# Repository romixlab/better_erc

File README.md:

# better_erc

Electrical rule checks for schematics that go further than the ERC built into an EDA tool: checks that know
what an I2C bus, a pull-up, a MOSFET or a power rail is, read from the netlist your EDA tool exports. Plus
`berc textconv`, which makes `git diff` of KiCad files readable.

For hardware engineers who review schematics (their own or someone else's) and want the repetitive part of a
review done by a tool, and for teams that keep KiCad projects in git.

The project is early. The KiCad diff tool is ready for daily use; the checks run from the shell and in CI with
`berc check` and as a Rust library; the desktop app is a first prototype.

## What works today

- **`berc textconv`**: `.kicad_sch`, `.kicad_pcb` and `.kicad_pro` files as sorted, line-oriented text for
  `git diff`, `git log -p` and anything else that uses git's textconv. See
  [Readable git diffs](#readable-git-diffs).
- **Import** into one board model ([docs/model.md](docs/model.md)): KiCad 8, 9 and 10 projects, schematics, boards
  and netlists read by better_erc itself (`erc_kicad`), OrCAD Capture netlists (pstxnet, pstxprt, pstchip), Altium
  EDIF plus WireList, Altium Smart PDFs (the netlist in their bookmarks: vendor boards that come as nothing but a
  PDF), and pick-and-place CSV files from KiCad, Altium and Allegro (`erc_import`), all picked by one importer
  registry.
- **Checks** (`erc_checks`), run on a KiCad project read by better_erc itself (`erc_kicad`), with one finding
  type, a report of which checks ran and which could not run for lack of data, and the report as JSON or text
  ([docs/engine.md](docs/engine.md)):
  - I2C buses found from net names, including segments behind ties and voltage translators; missing, redundant,
    unequal or out-of-range pull-ups, pull-ups through series resistors to nowhere, series resistors that are
    too large (`I2C-1`, `I2C-2`, `I2C-3`, `I2C-7`, `I2C-9`, `I2C-10`)
  - parts without a value, placeholder values like `?` or `TBD` (fitted or not), resistor values that don't read
    or are written in a non-standard way (`BOM-5`, `BOM-6`, `BOM-9`, `BOM-10`)
  - MOSFET symbols whose pins aren't named G, S and D (`LIB-3`)
- **`berc check`**: the checks on a KiCad project (or a KiCad netlist, Altium, OrCAD, Smart PDF or PnP file) from the shell
  or a CI job, as text, JSON, SARIF (GitHub code scanning) or Markdown (a PR comment), with an exit code by
  severity and a baseline so only new findings fail. `berc explain ID` and `berc checks list` show the catalogue.
  See [Checks in CI](#checks-in-ci).
- **`berc diff --pnp A B`**: two pick-and-place files, two boards, or a board and the PnP file exported from it
  compared footprint by footprint (position, rotation, side, value, package), with tolerances.
- **`berc diff --nets A B`**: the nets of any two designs (a schematic, a netlist, an Altium export, a Smart PDF)
  compared as the pins each net connects, whatever their names: renamed, removed and added nets.
- **`berc fp`**: footprint review. `berc fp hash` prints a footprint's review hash, the same for a library file and
  every board copy of it; `berc fp check` checks every board footprint against the hash on its library symbol (and
  against its library footprint), `berc fp check --lib` every symbol of a symbol library against its library
  footprint, and `berc fp todo` lists the library symbols a board uses that need a review; `berc fp model` reads
  each footprint's 3D models and measures them against it. See [Footprint review](#footprint-review).
- **The app** (`better_erc`, egui, crate `better_erc_app`): an import tab that opens any design the registry reads
  (and Altium or OrCAD files picked one by one) and shows its findings with their explanations and the checks that
  did not run, and tabs for nets (power rails, grounds and switching nodes from names and pin types), I2C buses,
  style findings and inputs; a footprint review tab that draws a library symbol's footprint over its datasheet
  drawing and writes the review hash into the symbol (see [Reviewing in the app](#reviewing-in-the-app)).
- **Signal levels** (crate `erc_levels`): a database of the levels logic families, buses and differential
  standards define (74xx and CD4000, JEDEC LVCMOS/SSTL/HSTL, I2C, RS-485, CAN, LVDS, ECL, USB, Ethernet and more),
  every number with the document, table and page it was read from. See [docs/signal-levels.md](docs/signal-levels.md).
- **The library** (crate `better_erc`): all of the above for Rust code in one dependency.

## Documentation

- [docs/checks.md](docs/checks.md): the check catalogue, everything better_erc should catch on a schematic or
  netlist, by ID (`PIN-1`, `I2C-3`) and severity.
- [docs/engine.md](docs/engine.md): the check engine: checks and their data needs, findings, the report, the test
  schematics with their expectations, how to add a check.
- [docs/model.md](docs/model.md): the board model, the importers and the crates.
- [docs/drawing-guide.md](docs/drawing-guide.md): how to draw a sheet that reads at a glance (signal flow, power and
  ground, grid, labels, text, title block, KiCad shortcuts), each rule with its reason and source, and our own sheets
  measured against it; the `DRAW` checks automate part of it.
- [docs/signal-levels.md](docs/signal-levels.md): the signal-level database: its format, where each number comes
  from, what `verified` means, and how to add a family.
- [docs/review-checklist.md](docs/review-checklist.md): a condensed schematic review checklist that groups those
  IDs for a review pass.
- [FEATURES.md](FEATURES.md): what the code does today and what is planned, item by item.
- [CHANGELOG.md](CHANGELOG.md): what changed in each version.

## Install

You need a Rust toolchain (1.86 or newer, from [rustup](https://rustup.rs)). From a clone of this repository, with
[just](https://github.com/casey/just): `just install` works anywhere and builds both binaries; with our release
tool on PATH it uses that (one copy kept on PATH), otherwise `cargo install`. Or by hand:

```sh
cargo install --locked --path berc             # the berc command line tool
cargo install --locked --path better_erc_app   # the desktop app (binary better_erc)
```

`berc --version` shows the version,
the git commit it was built from and that commit's time.

## Quick start

Readable diffs of a KiCad project in git, once per machine and once per repository:

```sh
git config --global diff.kicad.textconv "berc textconv"
printf '*.kicad_sch diff=kicad\n*.kicad_pcb diff=kicad\n*.kicad_pro diff=kicad\n' >> .gitattributes
git diff   # changed parts, values, nets and settings instead of raw s-expressions
```

Run the checks on a KiCad project (its directory, or the `.kicad_pro` / `.kicad_sch`):

```sh
berc check hw/board                  # findings worst first, the checks that could not run and why
berc explain I2C-3                   # what a check catches, why it matters, how to fix it
berc checks list --project hw/board  # every catalogue check: ran, not run (and why), planned
```

From Rust, the same run is `erc_checks::check_path` (or `erc_checks::Project::open` and `check`), see
[docs/engine.md](docs/engine.md).

Start the app with `just run` (or `better_erc` once installed).

Shell completion for `berc`: add `source <(COMPLETE=bash berc)` to `~/.bashrc`, `source <(COMPLETE=zsh berc)`
to `~/.zshrc`, or `COMPLETE=fish berc | source` to `~/.config/fish/config.fish`.

## Checks in CI

```sh
berc check PROJECT [--variant V] [--only CAT,ID] [--format text|json|sarif|md]
                   [--baseline report.json] [--fail-on error|warning|suggestion] [--require NEED]
                   [--set NAME=VALUE] [--theme THEME.json]
```

`PROJECT` is a directory with one design in it (its `.kicad_pro`) or a design file. Exit codes:

| code | meaning |
|---|---|
| 0 | no finding at or above `--fail-on` (default `error`) |
| 1 | findings at or above `--fail-on`; with `--baseline`, only findings that are not in the baseline count |
| 2 | usage or import error: no such path, several designs in the directory, an unreadable file, an unknown variant or check, a baseline of another schema |
| 3 | a `--require`d need is not available on a board (`--require layout` without a `.kicad_pcb`); wins over 1 |

`--format json` writes the report with its versioned schema; that file is also what `--baseline` takes: findings are
matched by board and fingerprint (check id and the names of the nets and parts involved), marked new or unchanged,
and the fixed ones listed. `--format sarif` writes SARIF 2.1.0: one rule per catalogue check, error → `error`,
warning → `warning`, suggestion → `note`, each finding located at the schematic file and the line of its symbol
(the file alone where no line is known). `--format md` is a summary for a pull request comment. `--state` is
reserved for power states and refused until they exist.

A GitHub Actions job that fails on errors, shows the findings in code scanning on the schematic files and puts the
Markdown summary on the run page:

```yaml
name: schematic checks
on: [push, pull_request]
jobs:
  berc:
    runs-on: ubuntu-latest
    permissions:
      contents: read
      security-events: write # upload SARIF to code scanning
    steps:
      - uses: actions/checkout@v4
      - uses: dtolnay/rust-toolchain@stable
      - run: cargo install --locked --git https://github.com/romixlab/better_erc berc
      - name: berc check
        run: berc check hw/board --format sarif > berc.sarif
      - name: Summary
        if: always()
        run: berc check hw/board --format md >> "$GITHUB_STEP_SUMMARY" || true
      - name: Upload to code scanning
        if: always()
        uses: github/codeql-action/upload-sarif@v3
        with:
          sarif_file: berc.sarif
          category: better_erc
```

Run it from the repository root with a relative project path: the SARIF file names the schematic files relative to
the current directory, which is what code scanning expects. To adopt better_erc on a board with known findings,
commit a baseline (`berc check hw/board --format json > hw/board/berc-baseline.json`) and add
`--baseline hw/board/berc-baseline.json`: from then on only new findings fail the job.

In this repository `just check` runs `berc check` on the test schematics against the committed
`test_schematics/berc-baseline.json` (they have findings on purpose), and `just check-baseline` rewrites it.

## Footprint review

A footprint checked once against its datasheet should not have to be checked again on the next board, unless it
changed. `berc fp` keeps that record as a hash on the library symbol.

`berc fp hash` prints a footprint's review hash, `fp1:` and 16 hex digits:

```sh
berc fp hash Lib.pretty/SOT-23.kicad_mod          # a library footprint
berc fp hash board.kicad_pcb U3                   # a footprint on a board, by its reference
berc fp hash board.kicad_pcb U3 --canonical       # and the text the hash is taken over
```

The hash covers what a review checks against the datasheet:

- every pad: number, type, shape, size, position, rotation, drill and its offset, layers, mask, paste, clearance and
  thermal settings, corner and chamfer ratios, custom pad shapes;
- the footprint's clearance, mask and paste settings;
- graphics on copper, mask, paste, courtyard and `Edge.Cuts` layers, zones and keepouts.

Silk, fab and user layers, texts, the 3D model and where the footprint sits on a board don't count. A board copy is
brought back to the footprint's own frame first (position, rotation and a flip to the back undone), so it has the hash
of its library file. Lengths are compared on a 100 nm grid and items in a fixed order, so a re-save in another KiCad
version or a reorder never changes the hash. The `fp1:` prefix is the version of these rules: a later change of them
gives `fp2:` hashes, and an `fp1:` hash then reads as made by another version instead of as a mismatch. The hex digits
are the first 8 bytes of the SHA-256 of the canonical text (`--canonical`, lines joined by a newline): a short
fingerprint to tell a footprint unchanged, not a signature.

Once a footprint is reviewed, `berc fp accept` puts its hash in the `Footprint_Review` field of the library symbol
that uses it (see [Accepting a review](#accepting-a-review)), or the app's Accept does. `berc fp check` then checks a
board:

```sh
berc fp check                       # the KiCad project in this directory
berc fp check hw/board --format json
```

For each footprint on the board it reads the review hash from its symbol's library symbol: in the `.kicad_sym`
found through the project's or the global `sym-lib-table`, else in the schematic's copy of the library symbol. Each
footprint is one of:

| Status | Meaning |
|---|---|
| ok | the footprint is the one reviewed |
| changed | the footprint differs from the one reviewed: review it again (with several review lines, the stale ones are named) |
| partial | every review line's hash matches, but some of the symbol's MPNs are on no line: their datasheets are not reviewed yet, named |
| unreviewed | the symbol has no review hash; the line shows the hash to put there once reviewed |
| refused | the symbol sets no footprint, so a review of the one on the board means nothing |
| no symbol | the footprint has no schematic symbol and is not marked board-only |
| board-only | no symbol, marked board-only in KiCad (logos, mounting holes): listed last under its own heading, not a failure |
| other version, malformed | the field holds a hash of another version, or no hash at all |

A schematic copy that holds a different hash than the library is reported as well: the schematic was not updated
from the library. So is a board copy that differs from its library footprint (the footprint the board names, found
through `--footprints` and the `fp-lib-table`; a board footprint without a library nickname is looked up by its
symbol's `Footprint` field): the line shows both hashes, and the board was not updated from the library.

A board footprint placed under a different `Lib:Name` than its symbol's own `Footprint` field (a library migration
half done, or a deliberate per-instance override) is reported too, naming both: a library migration that renamed or
moved a footprint library, left half done, or a board edited by hand without updating the schematic, looks exactly
like this. A footprint placed with no library nickname at all is not an override, there being nothing to compare its
name against. Footprints that could not be compared are summed up once per reason below the list. `--symbols DIR` adds symbol libraries (a
`.kicad_sym`, a `.kicad_symdir` or a folder of them, each named by its file name) searched before the
`sym-lib-table`, and `--footprints DIR` footprint libraries searched before the `fp-lib-table`, for a PC without
KiCad's global tables:

```sh
berc fp check hw/board --symbols ~/kicad-library/symbols --footprints ~/kicad-library/footprints
```

The exit code is 0 when every footprint is ok or board-only and every copy up to date, 1 otherwise, 2 when the
project can't be read.

### Review lines: where a review was made

A review is made against one datasheet, and a datasheet is one maker's: the MPNs of one maker usually share one, and
two makers never do. So a symbol holds one review line per datasheet, each in a property of its own,
`Footprint_Review`, `Footprint_Review2`, `Footprint_Review3`, ... (KiCad needs field names unique, as with `Mpn1`,
`Mpn2`). Each is one line, the review hash first and where the review was made after it:

```text
fp1:7726812df851763a mpn=BSS138W-7-F,BSS138WQ-7-F doc=DS30154@rev16 pdf=b3:0123456789abcdef page=3 scale=0.02 at=150,230,90,mirror by=roman on=13nov2026
```

| Key | What |
|---|---|
| `mpn=` | the MPNs this datasheet covers, from the symbol's `Mpn`, `Mpn1`, `Mpn2`, ... fields, comma-separated; a comma, `%` or blank inside one is written `%2C`, `%25`, `%20` (Nexperia's `BSS138BKW,115` is `BSS138BKW%2C115`). No `mpn=`: the line reviews the whole symbol |
| `doc=` | the document number and revision, where the document library knows them: they survive a download of the same document with other bytes |
| `pdf=` | the PDF by the document library's content hash: `b3:` and 16 hex digits of its blake3 |
| `page=` | the page the land pattern is on, 1-based |
| `scale=` | the drawing's scale on that page, mm per PDF point |
| `at=` | where the footprint lay on the page: its origin in page points from the page's top left, its rotation in degrees, `mirror` when seen from below |
| `by=`, `on=` | who reviewed it, and the day |

The MPNs are written as strings, so reordering the `Mpn` fields breaks nothing. A key this version doesn't know stays
on the line as it is. `berc fp check` reads the first token of each line as its hash: a symbol is ok when every line's
hash is the footprint's and every MPN of the symbol is on some line (a symbol without `Mpn` fields needs a line
without `mpn=`); otherwise it lists the MPNs not reviewed yet (partial) and the stale lines (changed). A value with
the hash alone, as written before lines had a source, stays valid: a review of the whole symbol with no source
recorded. `--details` prints every line under its footprint or symbol, with its status:

```sh
berc fp check hw/board --details
berc fp check --lib Device --details
```

`--format json` holds each line read (`reviews.lines`: property, value, its parts, status) and the MPNs not reviewed
(`reviews.unreviewed_mpns`). `berc textconv` shows each line whole.

### What to review for a board

`berc fp todo` lists the library symbols a board's footprints come from, once each, and what each needs. The review
is of the library: each symbol is checked as `berc fp check --lib` checks it, against the library footprint its
`Footprint` field names, so a symbol reviewed once is done for every board that uses it.

```sh
berc fp todo                       # the KiCad project in this directory
berc fp todo hw/board --symbols ~/kicad-library/symbols --footprints ~/kicad-library/footprints
berc fp todo hw/board --format json
```

The symbols to review come first, in the order to step through them: changed (reviewed before, the footprint moved
on), other version, malformed, unreviewed, partial (an MPN's datasheet not reviewed yet); by symbol within each. Each line shows the footprint, the hash it gets once
reviewed and the board references that use it, and (always shown, whatever the symbol's own status) the references
whose board places a different footprint than this line's, the same `Lib:Name` mismatch `berc fp check` names.
Below them, under their own heading, the symbols that can't be
reviewed until fixed: missing (the library symbol or its footprint is not found, the line says why) and refused. The
ok ones and those without a footprint are counted; `--all` lists them too. `--format json` always holds every symbol
with its footprint file, the hash now and the `Datasheet` field, for the app's review tab and scripts; the library
call is `better_erc::fp::todo`. A symbol whose board places another footprint than its own carries that one too:
`placed`, its library file `placed_file` and hash now `placed_hash`, or `placed_note` saying why no library has it.
`files` lists every file the list was made from (what the app's review tab watches). The exit code is 0 when there is nothing to review or fix, 1 otherwise, 2 when the
project can't be read.

### Accepting a review

`berc fp accept` writes the review hash of board footprints into their symbols:

```sh
berc fp accept hw/board U1 U2           # the hash of U1 and U2 now, into their library symbol
berc fp accept hw/board U1 --dry-run    # what would be written, nothing written
berc fp accept hw/board --symbol Device:R --hash fp1:0123456789abcdef
berc fp accept hw/board U1 --footprint VHRD_Package_QFP:LQFP-48   # also sets the symbol's own Footprint
berc fp accept hw/board Q1 --mpn BSS138W-7-F --mpn BSS138WQ-7-F --doc DS30154@rev16 --page 3
```

`--mpn` (repeatable), `--doc`, `--pdf` and `--page` say where the review was made: the review line of that
datasheet is written (see [Review lines](#review-lines-where-a-review-was-made)), with `by=` (`--by`, else the
login name) and today's date. Among the symbol's other lines, a line about the same datasheet (the same `pdf=`, or
the same document number) is replaced in its place; the MPNs it names leave the other lines, and a line left with
none goes; a line with the hash alone goes once lines with MPNs cover every MPN; a new line goes last. Without
them, the line is for the whole symbol and replaces the lines without MPNs, except another datasheet's: a line
naming another document stays. Every file gets the same lines, and a review
property left over past them is removed.

`--footprint LIB:NAME` also sets the library symbol's own `Footprint` field to it, the value `berc fp check` showed
as the one the board places: written the same way as the review hash, into the library and every schematic copy.
Given for references of more than one library symbol at once, it is refused: one value can't hold for several.

The review line goes into the `Footprint_Review` fields of each footprint's schematic symbol's library symbol, in two places:
the library's `.kicad_sym` (or the symbol's file in a `.kicad_symdir`), found through the project's or the global
`sym-lib-table`, and the copy of the symbol in every schematic sheet's `lib_symbols`, so `berc fp check` finds both
up to date. A library that is not found is named in the output, and only the schematic copies are written.

The `sym-lib-table` lookup follows the library wherever it actually lives, even for a project copied somewhere else
to try `accept` on: running it against a scratch copy of a project still writes into the real library the table
points at, not a copy of it, `--symbol`/`--hash` included. To try `accept` without touching the library in place,
copy the library too and rewrite the copied project's `sym-lib-table` (or the global one in KiCad's configuration
directory) to point at that copy.

Only the field is written. Every other byte of each file stays as it was, so the file's diff is the one field. A
field that is there gets its new value; a new field goes after the symbol's own fields, hidden, laid out as the
KiCad version that wrote the file lays it out (checked against kicad-cli in the tests). KiCad 8, 9 and 10 files are
written; an older file is refused until KiCad 8 or newer saved it. Each file is replaced through a temporary file
beside it. A library open in KiCad's symbol editor shows the field once it is opened again.

Nothing is written when anything is wrong:

- a symbol placed with more than one footprint (a generic `Device:C` on 0402 and 1210 pads): one hash can't hold
  for all of them;
- footprints of one symbol whose board copies differ;
- a symbol that sets no footprint, a footprint without a schematic symbol, a hash that is not `fp1:` and 16 hex
  digits.

The exit code is 0 when written (or nothing needed a change), 2 otherwise. `--format json` lists every file with its
old value.

### Checking a symbol library

`berc fp check --lib` checks a symbol library itself, before any board uses it: each symbol against the library
footprint its `Footprint` field names.

```sh
berc fp check --lib symbols/Lib.kicad_symdir --footprints footprints
berc fp check --lib symbols --footprints footprints   # every library in the folder
berc fp check --lib Device hw/board                   # a nickname from hw/board's or the global sym-lib-table
```

`--lib` takes a `.kicad_sym` file, a KiCad 9+ `.kicad_symdir` directory, a folder of them, or a nickname from the
`sym-lib-table`; it can be given more than once. A library given as a path is named by its file name
(`Lib.kicad_symdir` is `Lib`). The footprints are found through `--footprints` (a `.pretty` directory or a folder of
them, each named by its folder name, searched first), then the project's and the global `fp-lib-table`; the project is
the directory given, `.` by default. Each symbol is one of:

| Status | Meaning |
|---|---|
| ok | the footprint is the one reviewed |
| changed | the footprint differs from the one reviewed: review it again |
| unreviewed | the symbol has no review hash; the line shows the hash to put there once reviewed |
| missing | the footprint the symbol names is not found; the line says why |
| refused | the symbol has a review hash but sets no footprint, so the hash reviews nothing |
| other version, malformed | the field holds a hash of another version, or no hash at all |
| no footprint | the symbol sets no footprint and has no hash (a generic part, a power symbol): listed last, not a failure |

A derived symbol (`extends`) has its parent's footprint and hash unless it sets its own. The exit code is 0 when every
symbol is ok or has no footprint, 1 otherwise, 2 when a library can't be read.

`--allow NICKNAME` (repeatable, for `--lib` here and for `berc fp todo`) lists the library nicknames a symbol and its
footprint may be in: an exact name, or a prefix ending `*` (`--allow 'VHRD_*'`). A symbol's own library, or the one
its `Footprint` names, that is none of them is reported, naming it. Given none, there is no rule and nothing is
reported: a project only sets this once it has a library convention to enforce.

### 3D models against the footprint

`berc fp model` reads each footprint's 3D models (STEP) and measures them against the footprint: the third source of
truth beside the datasheet drawing and the footprint itself.

```sh
berc fp model hw/board                          # every footprint on the project's board
berc fp model hw/board U3 J1 --details          # these references, each pad's share under a lead
berc fp model ~/kicad-library/footprints/VHRD_Package_SO.pretty   # every footprint of a library
berc fp model Lib.pretty/SOT-23.kicad_mod --format json
```

Each `(model ...)` entry's file is found as KiCad finds it: `${VAR}` from the environment, KiCad's
`kicad_common.json`, `KIPRJMOD` (the board's directory, or the directory a library is in; `--project DIR` sets
it) and a stock KiCad's `KICADn_3DMODEL_DIR`; a `.wrl` tries `.step` and `.stp` beside it. The file is read
(`erc_step`) and placed as KiCad places it: the scale, then the rotation about x, y and z (each by the negated angle),
then the offset; a test holds this against `kicad-cli pcb export step`. For each model the command prints:

- the file and the variables that found it, or why it was not found;
- the file's unit, its parts and faces, and what the reader could not read (`--details` lists every warning);
- the extents in x, y and z, the height above the board and the depth below it (THT leads);
- the middle of the model against the middle of the pads;
- how far the model reaches out of the courtyard;
- whether the leads land on the pads: the model's bottom 0.2 mm seen from below against each pad's copper, how many
  pads have a lead over them and how much of the slice is off the pads (`--details`: each pad's share).

Coordinates are KiCad's 3D frame of the footprint in mm: x right, y up (the footprint editor's y negated, as the model
offset is written), z up from the board surface. The findings are catalogue checks: `LIB-22` model file missing or
unreadable, `LIB-23` out of the courtyard, `LIB-24` a pad without a lead, `LIB-25` scaled, `LIB-26` not in mm,
`LIB-27` turned by an angle that is not a multiple of 90°, `LIB-28` no model shown (`berc explain LIB-24`). The exit
code is 1 on any warning, 0 when there are only suggestions (no model, not in mm) or nothing, 2 on a read error.

### Reviewing in the app

The app's Footprint review tab does the review itself: it starts from a library symbol, since the symbol is what a
schematic places and what holds the hash, draws the footprint its `Footprint` field names over the datasheet's
drawing, and Accept writes the hash into that symbol's `Footprint_Review` field.

1. **Pick a symbol**: open a board or project (`.kicad_pcb`, `.kicad_pro`, `.kicad_sch`) for the library symbols
   its board uses, as `berc fp todo` lists them, those to review first; or a symbol library (a `.kicad_sym`, a
   `.kicad_symdir` folder, or a nickname from the `sym-lib-table`s) for its symbols. Each row shows the symbol's
   status (unreviewed, changed, ok, missing, no footprint). Picking one opens the library footprint its `Footprint`
   field names, found through the project's or the global `fp-lib-table`; from a board, when every reference places
   a different footprint than that field names, the one actually placed opens instead, noted above the canvas
   rather than left unsaid. That one too is read from its library file, since the review hash is the library
   footprint's; the note says when the board's copy differs from it (the board not updated from the library yet),
   and only a footprint no library table has is read from the board's copy. A symbol that sets no footprint, or whose
   symbol or footprint is not found, is refused with the reason. Next to review steps to the next symbol that
   needs one. A reviewed symbol lists its review lines (what each was made against, its MPNs, ok or stale) and the
   MPNs no line reviews yet.
2. **Open the datasheet**: the symbol's `Datasheet` field when it names a local file, a local document library
   search, or Open PDF. The library search runs a command (a setting) with the datasheet's file name, a part name
   in its web address, the `Mpn` fields or the value, until one finds something. The command prints a JSON list of
   `{"path": ..., "page": ...}`. What it finds is listed in a panel of its own, and for a symbol just picked the
   first one opens by itself. Picking another symbol opens its datasheet, or closes the last one when it has none.
   A symbol whose review recorded its datasheet opens that PDF first, found in the document library by its content
   hash, else by its document number, and with it the view the review was made in: the page, the scale and the
   footprint's placement. So does opening any datasheet a review line was made on. A line whose hash is no longer
   the footprint's is said to be stale, and a recorded PDF the library doesn't have is said too. The library's
   index comes from a command (a setting, `tpm lib docs --json --all` by default) that prints a JSON list of
   `{"path", "hash", "doc", "rev"}`, paths relative to the library's root; the file on disk is then found through
   the library name command below, which prints full paths.
   A symbol with `Mpn` fields gets a table, Datasheets by MPN, at the top of the Datasheet section: each MPN, the
   library document that covers it, and its review state (reviewed, reviewed elsewhere when its line was made on
   another document, stale, or not yet). Which document covers an MPN is the document library's answer, not
   better_erc's: a command (a setting, `library_mpn`, `tpm lib mpn --json` by default) gets the MPNs at the end and
   prints a JSON list of `{"mpn", "path", "hash", "doc", "rev", "why"}`, one object per document of an MPN, best
   first, or one with no `path` and `why` it has none. A series or catalogue file may cover several MPNs. Each MPN
   is asked once per session. Clicking a document opens it with the view of its review line, else the page search
   runs. An MPN without a document says why, and its Fetch button runs another command (`library_fetch`,
   `tpm lib fetch --mpn` by default) with the MPN, then asks about it again. There are no extra `Datasheet2..N`
   fields: the library holds the mapping.
   The page search then goes to the page with the land pattern, found by words such as "recommended land pattern"
   (a setting); the pages it found are listed to pick from. F shows the page at the view's full width.
3. **Set the scale**: R with the pointer at one end of a dimension of the drawing, R again at the other (or pick
   Scale on the mode bar and drag along it). The ruler snaps level: horizontal or vertical by the larger of its dx and dy, an end
   dragged goes where it is dragged and the other end follows on that axis (Shift held, or the setting off: any
   angle). Its ends snap to the drawing's own lines, read from the PDF's vector paths: within 10 screen pixels (a
   setting, 0 for never) to a line's end or two lines crossing, else onto the nearest line's centre; on a level
   ruler each coordinate on its own, so on a horizontal ruler an end takes the X of the extension line beside it
   and the Y of a line along it. Thin filled rectangles count as lines, and the edges of other filled shapes (a
   pad drawn filled) as lines too. Where an end would snap shows at the pointer before it is placed: the lines in
   orange, a square on an end, a cross on a crossing, a ring on a line. Alt held leaves an end where the pointer
   is. Z zooms in on the first end, where a click or a drag puts it exactly; Z again on the
   other end. The number the dimension prints between the ruler's ends, read from the page's text, is outlined
   and offered as a chip beside the ruler's length (`2.00 mm · D`): D or a click on it sets the scale from it. S goes back to the view and asks the length in a box in the middle of the canvas, the number typed
   shown large in mm: type the length and Enter sets the scale, Esc leaves the box without one (the side panel's
   field and Set scale do the same by mouse); Z a third time does what S does. The keys of the
   whole step: F, R, R, Z, Z, S, the length, Enter; with the snap and the dimension's number, often F, R, R, D. A page
   that states its own scale (`SCALE: 20X`) offers it as a button; check it with the ruler. Once the scale is set,
   the mode is Move again.
4. **Lay the footprint on the drawing**: drag it (the Move mode, M), nudge it with the arrow keys (Shift: ten times
   as far), turn it with T or ⟲ 90° or by an angle, mirror it with X for a drawing seen from below. Opacity, Blink
   (B) and Invert page (I, white-ish on black, for a dark drawing or just to see differently; the default is a
   setting) help to see both, and so does the blend mode: Normal (the footprint over the page by its opacity),
   Multiply (the drawing's lines stay dark through it), Screen, or Difference: with white copper (a setting),
   white paper under a pad goes black, so a footprint that covers the drawing's pads exactly leaves no light edge, and a pad that
   misses shows light (inverting the page keeps these meanings: Difference still reads the same, now on black).
   Three views show what the board makes on one layer, one view at a time (a radio choice, C cycles through
   them), each filled in its one colour: Copper (the pads' copper, the copper graphics and the package's vias,
   red), Mask (the mask openings only: each pad's by its margin, and the mask graphics, pink) and Paste (the paste
   apertures only, such as the windows of a split exposed pad, gray). The pads are not drawn outside the Copper
   view; holes and pad numbers are drawn over every view. The margins are the pad's, else the footprint's, else
   the open board's design settings (`pad_to_mask_clearance`, `pad_to_paste_clearance` and its ratio) for a
   footprint of that board or its project's libraries. Back pads (the back side in the same views), Courtyard,
   Fab, Silk and Board edge are shown or hidden each by its checkbox. The colours are settings only, with no
   picker in the tab. A package's vias (round plated pads without a number of their own, such as thermal vias in
   an exposed pad; KiCad has no vias in footprints) are copper with their holes; they are in the review hash as
   the pads they are.
   Scroll zooms at the pointer; the right or middle button pans; Page Up and Page Down turn pages. A help line
   under the canvas names the keys.
5. **Measure and write notes**: a bar above the canvas shows the modes, each with its key, the one on highlighted
   and named first in the help line: Move (M: the mouse moves the footprint), Scale (R: the ruler that sets the
   scale), Measure PDF (E: the ruler on the drawing's lines, snapping as the scale's does) and Measure footprint (G:
   the ruler on the footprint, its ends snapping to the pads' centres and, on rect and roundrect pads, to the middle
   of each side, where the pad's centre cross meets its edge; a cross in a ring marks a centre, a diamond a side).
   Esc, M or a mode's own key again go back to Move. A measuring ruler shows its length with dx and dy, and once let
   go its length goes into the review note as `M1 = 1.234 mm`; moving an end changes that value, a new ruler is `M2`.
   The scale's ruler waits while measuring and is back in Move. The note field sits above the canvas; Enter over the
   canvas gives it the keyboard, and Enter in it (or Add) appends the note to the notes file: a Markdown section per
   note with the symbol, the footprint, the datasheet and its page, the time (UTC) and the text. The file is a
   setting, by default `footprint-review-notes.md` beside the project or library under review (an absolute path puts
   it anywhere). The datasheet is named as the document library names it, by a command (a setting; `tpm lib open
   --json` by default) that prints a JSON list of `{"path", "value", "doc_no", "doc_rev"}`: by its document number and
   revision where they are known (`` `tpm d DS13560 rev6` ``, which still finds it after a rename or a move), else by
   the words that open it, else by its file. The next note's measurements count from M1 again.
6. **Select and save as DXF**: Select (V), the fifth mode, picks pieces of the datasheet's drawing as the PDF draws
   them: a line, a polyline, an arc or curve, a closed shape. A click picks the piece under the pointer (inside a
   filled shape counts), again drops it; a click on nothing drops them all. A drag selects what lies wholly inside
   its box; Shift adds to the selection. The pieces selected are drawn over the page in cyan, the one a click would
   pick in a lighter cyan. Save DXF (W, the button under the mode bar, or the pie) writes them as a DXF beside the
   notes file, `<symbol>-p<page>-<n>.dxf`, and appends `` DXF `Rev_Mixed-p2-1.dxf` `` to the note, so the note links
   to it. The DXF is in the footprint's millimetres: the page's points go through the scale and back through the
   footprint's placement (origin, rotation, bottom view), so KiCad's footprint editor, File → Import → Graphics at
   0, 0, drops the drawing in place over the pads (DXF's Y points up; the import turns it over). It is R12 ASCII
   (LINE, ARC, CIRCLE, POLYLINE) with a few comment lines naming the symbol, the footprint and the page, so an agent
   reads it as text too. Curves become arcs and circles where they follow a circle within the DXF curve tolerance (a
   setting, 0.005 mm), any other curve becomes straight pieces within it. Save stays disabled, saying why, until
   something is selected, the scale is set on the page shown and a footprint is shown.
7. **The 3D model and Measure model**: 3 (a setting, the 3D button in the mode bar, the pie) swaps the canvas between
   the page and the footprint's 3D model. The STEP files of its `(model ...)` entries are found and read as `berc fp
   model` does, on a worker thread, and placed as KiCad places them: on a 1.6 mm board whose top is z 0, with the
   front pads' copper on it. Drag turns the model, the right or middle button pans, the wheel zooms at the pointer, a
   double-click turns about the point under it, a right-click gives the preset views; the SpaceMouse drives all six
   axes there. Measure model (O, the sixth mode, which shows the model by itself) measures on the faces and edges as
   the STEP file writes them, not on the triangles: a click picks a face or an edge, a second click another. Two
   parallel planes give their distance and two planes at an angle the angle; two cylinders, holes or circles the
   distance of their axes (a pin pitch); a plane and an axis parallel to it the axis' height; a plane and anything
   else the point's height over it; the same cylinder or circle twice its diameter, the same edge twice its length;
   anything else the straight distance. The result is drawn on the view and goes into the review note as `M3 = 1.270
   mm (pitch, axis to axis)`, numbered with the rulers' measurements. What is under the pointer shows at the top of
   the view (`pad 2: plane facing +Z at z 0.035 mm`, `part: hole Ø 0.800 mm`). The side panel's 3D model section
   names each file with its parts, faces, size and height, and what could not be read. A footprint that names no
   model, or a file not found, says so in the view and the section.
8. **The model's views over the page**: the model's top, bottom, front, back, left and right views drawn over the
   datasheet at the page's scale, to hold against the package drawing. Each is the model's silhouette filled in its
   colour (a setting, `colors.model`), outlined, with the edges seen from that side (`colors.model_edges`); edges
   hidden behind a face are left out. The top view lies as the footprint does, the side views stand on the board's
   line through the origin, the bottom view is mirrored as a package drawing's is. K (a setting, the Moves button in
   the mode bar, the pie) picks what moves: the footprint, then each view in turn, then the footprint again; the view
   picked is shown, the top view first on the footprint and the others in the middle of the canvas. What moves is
   what the mouse in Move, the arrow keys, turn (T) and mirror (X) move and what the Placement section shows; each
   view keeps its own place, all share the page's scale. The side panel's Model views section shows and hides each
   view, picks what moves, and sets the views' blend mode (normal, multiply, screen, difference), opacity and blink
   (B blinks what moves). Measure footprint (G) snaps to the views' outline corners and edge ends too, so a model
   dimension measures on the page. The footprint is drawn over the views where they overlap.
9. **Accept** (A): when the footprint matches the drawing, Accept writes its review line into the symbol: the library
   symbol and, for a symbol from a project's list, the schematic's copies too (as `berc fp accept --symbol` does).
   The line records where the review was made: the datasheet by the document library's content hash and document
   number, the page, the scale, the footprint's placement, who (a setting, else the login name) and the day. It
   asks first which of the symbol's MPNs this datasheet covers, those found in the PDF's text (and those the
   line for this datasheet already names) ticked, except an MPN another datasheet's line names: the question says
   which, and ticking it moves it here; none ticked makes a line for the whole symbol. Each datasheet keeps its own
   view of the symbol (page, zoom, scale, placements, ruler, note), saved with the tab: opening another datasheet
   and coming back finds the first as it was left, accepted or not. It shows what
   its dry run would write, following the ticks: each file, each property, the old and the new value. When the
   board places a different footprint than the symbol's own `Footprint` field, a checkbox offers to also set that
   field to the placed one, showing both; checked, it writes the same as `berc fp accept --footprint` does.
   Enter (or
   Write) writes; Esc (or Cancel) writes nothing. It warns, per file and naming the lock file, when KiCad may
   overwrite the change on its next save: a file with KiCad's lock file beside it (`~name.kicad_sch.lck`, open in
   an editor there) that is held. A lock from this computer is held while a KiCad runs here (KiCad's locks name
   the user and host, no process id; a lock with a `pid` while that process lives); one from another computer
   always counts; an empty one is stale, as KiCad takes it. KiCad running with no lock beside the file is no
   warning.
   Once written, it lists the files written, or says why it wrote nothing, copies the hash to the clipboard and keeps the review
   (symbol's footprint, hash, datasheet, page, scale) in the tab's list. Accept stays disabled, saying why, until a
   symbol with a footprint is picked, a datasheet is open and the scale is set on the page shown.

#### Files changed on disk

The tab shows the files as they are on disk. It watches every file it read: the board and its schematics, the library
tables, the symbol libraries, the footprint files, the 3D models and the datasheet. A file saved in KiCad or another
editor is read again by itself once it stays quiet for a moment, and picking a symbol or a board footprint looks at
the files first. Reload (`F5`, a setting, or the button under the Open buttons) reads everything again; a line beside
it says what was read again and when. A reload keeps the view: the page, the scale, the footprint's placement, the 3D
camera and the list's filter. The review status follows the file, so a footprint changed since its review shows the
review as changed. A file counts as changed only when its content changed; what Accept writes into the symbols reloads
nothing.

#### With a SpaceMouse

A 3Dconnexion SpaceMouse drives the review through [spacenavd](https://spacenav.sourceforge.net/), the free driver
(`sudo pacman -S spacenavd`, `sudo systemctl enable --now spacenavd`; other distros: their spacenavd package). The
app reads spacenavd's socket itself ([ve_spacemouse](https://github.com/vhrdtech/vhrd_egui), pure Rust, no
libspnav), so the device is not needed to build or run it.

- **The puck moves the page**: slide it and the page follows the hand, lift it and the page moves up, push it away
  and the view zooms out about the pointer (pull it towards you to zoom in). The slide pans in screen points, so a
  push moves the page across the screen at the same speed at every zoom. P switches the puck to move the footprint
  over the page instead, at the same screen speed; zooming stays the view's.
- **Tap a button**: the left one lays the ruler (R at the pointer: once for the first end, again for the other), the
  right one switches what the puck moves (P).
- **Hold a button**: a pie menu opens at the pointer. Move out across its outer circle, or click, to do the action
  under the pointer; while the button is held, back through the middle and out again does the next one. The left
  button's ring has the page and the ruler (full width, zoom on a ruler end, type the length, the dimension's
  number, back to Move, measure the PDF, select the drawing, next and previous page, invert the page); the right
  one's the footprint (turn 90°, bottom view, blink, copper/mask/paste, measure the footprint); both buttons together
  Accept, Next to review, Write a note and Save the selection as DXF. Every slot names its
  action and its key (`Turn 90° · T`); a slot that can't be used now is drawn muted and says why under the menu
  ("No ruler yet: R lays one, or the left button's tap"). While Accept's question is open, the left tap writes
  and the right one cancels.
- **Calibrate…** (SpaceMouse, in the tab's side panel) measures which way the puck reads and which button is which:
  it asks for one motion at a time (slide right, lift up, push away, each button), works the mapping out from what
  it recorded and shows a table to confirm. The side panel says whether spacenavd is there and, when not, what to do.
- **One mapping for every app**: the mapping (axes, signs, dead zone, speeds, buttons) is not the app's own but
  ve_spacemouse's shared `spacemouse.toml`, the same settings panel as in every app on it. It is read from
  `.config/spacemouse.toml` in the folder the app started in and each parent, then `~/.config/spacemouse.toml`,
  merged key by key with the nearest file winning, as Cargo reads its config. The panel shows which file each value
  comes from; Save (and a used calibration) writes to every folder's file, `~/.config/spacemouse.toml`, or to this
  project's. A `[spacemouse]` section that `config.toml` kept up to 0.4.42 moves into `~/.config/spacemouse.toml`
  at the tab's first start, once: keys that file already has keep their values, then the section leaves
  `config.toml` (the settings' note says what moved).

A footprint opened alone (Open a footprint alone, a `.kicad_mod`) or picked from a board's footprint list is a
preview: it is drawn over the datasheet the same way, but there is no symbol to put the hash on, so Accept is
disabled and says so. For a board footprint the tab says whether the board copy is the same as its library file.

PDFs are read and drawn by [hayro](https://github.com/LaurenzV/hayro), in pure Rust, on a thread of its own. The
blend modes other than Normal are a wgpu shader that reads the page's own pixel under the footprint. The
PDF standard fonts that a datasheet uses without embedding them come from the Liberation fonts when installed, else
from egui's own font.

The settings (blink rate, the opacity, blend mode and colours at first, whether the page is inverted at first,
the page search words, the finest drawing scale, the font folders, the library search command, the library name
command and the notes file, the library docs command (`library_docs`), the MPN lookup and fetch commands (`library_mpn`,
`library_fetch`) and the reviewer (`reviewer`) for the review
record, the allowed library nicknames (`allowed_libraries`, the app's side of `--allow`, none
by default), how far Z zooms in, whether the ruler snaps level, how near its ends snap to the
drawing's lines, the DXF curve tolerance, and the keys F, M, R, E, G, Z, S, D, T, X, B, C, I, P, A, N, Enter, V, W, 3, O and K
by name in
`[footprint_review.keys]`; a file that still has M for the bottom view takes X for it) are in
`~/.config/better_erc/config.toml` (`$XDG_CONFIG_HOME`, or the file `$BERC_CONFIG` names), section
`[footprint_review]`; the tab's Settings shows and saves them. The SpaceMouse's mapping is in `spacemouse.toml` (above). Each step of a review
is recorded in berc's usage record (`app fp-review accept`, `app fp-review write`, ...), which `berc usage` counts in its `app` column.

## Development

The workspace has the crates of the core, `erc_model` (the board model, value parsing, the netlist and placement
comparisons), `erc_kicad` (KiCad read by us), `erc_import` (the importer registry with Altium, OrCAD and PnP),
`erc_analysis` (part classes, graph queries, power structure, I2C buses) and `erc_checks` (the engine, the checks,
the report and its formats); `better_erc`, the library that re-exports them; `berc` (the command line tool) and
`better_erc_app` (the app, binary `better_erc`), both on the library.
`test_schematics` holds a small KiCad schematic per check; the differential test exports them with `kicad-cli`
and is skipped with a message where KiCad is not installed.

```sh
just test       # all tests
just lint       # clippy with warnings as errors, and the format check
just fmt        # format the code
just run        # start the app
just check      # berc check on the test schematics, against their baseline
just netlists   # export the test schematics to netlists and pictures
just            # list every recipe
```

## Readable git diffs

`git diff` of a `.kicad_sch`, `.kicad_pcb` or `.kicad_pro` is mostly noise: UUIDs, instance paths, coordinates,
items written in a new order on every save, and - for the project file - dozens of new-but-default settings
added the moment a newer KiCad opens and saves an older project. `berc textconv` turns one KiCad file into sorted,
line-oriented text (one fact per line, no UUIDs, no coordinates), and git can diff that instead. The stored files
don't change; `git diff`, `git log -p`, `git show` and lazygit all show the readable form.

A `.kicad_sch`'s cached library symbols (`lib_symbols`) print their fields - `Datasheet`, `Footprint`,
`Footprint_Review`, ... - as their own `Name=value` lines, a hash underneath for the rest of the symbol (pins,
graphics, sub-symbols). `berc fp accept` (see [Accepting a review](#accepting-a-review)) writes the
`Footprint_Review` field into every sheet's `lib_symbols` copy, so this is what turns an accepted review into a
one-line diff instead of a changed hash taken on faith.

With `berc` installed (see [Install](#install)), tell git which files to convert, in the repo with the KiCad
files (`.gitattributes`, committed, or `.git/info/attributes` for yourself only):

```gitattributes
*.kicad_sch diff=kicad
*.kicad_pcb diff=kicad
*.kicad_pro diff=kicad
```

And how to convert them, once per machine:

```sh
git config --global diff.kicad.textconv "berc textconv"
```

No `diff.kicad.cachetextconv`: `berc textconv` is fast enough that caching it isn't worth the staleness it buys
(0.12 s on a 17 MB `.kicad_pcb`, 8 ms on the largest `.kicad_sch` of a real hardware repository). `cachetextconv`
would keep the converted text in git notes (`refs/notes/textconv/kicad`), per blob and per textconv command: git
stores the command as the cache's validity and drops the cache when the configured command differs. A `berc`
upgrade keeps the same command, so after one that changes the output format, old blobs keep showing their old
(but still cached) text until the command changes or the notes ref is cleared.
`git diff --stat` and `--numstat` still count raw lines; that is git, not berc. To see the raw diff once, pass
`--no-textconv`.

Turning `cachetextconv` on anyway (a very large repository, a slow disk): clear the cache once per clone after
every `berc` upgrade that changes textconv's output:

```sh
git update-ref -d refs/notes/textconv/kicad
```

What the text shows:

- Schematic: title block; sub-sheets with file, page and pins; every symbol as
  `R104 10k  lib=Device:R  fp=Resistor_SMD:R_0402_1005Metric  dnp  no_bom` with its fields under it (sorted), units
  of one part grouped, pin alternates, and variant overrides only where they differ from the symbol; power symbols
  counted per net; no-connects by the pin they sit on (`nc U201.5 PA3`); labels, global and hierarchical labels
  counted; text and text boxes in full (newlines as `\n`); tables as rows; wires, junctions and graphics counted;
  a short hash per library symbol, so an edited symbol shows as one changed line.
- Board: stackup, design rules and plot settings one per line; every footprint as
  `C206 100nF  fp=Capacitor_SMD:C_0402_1005Metric  side=top  rot=90  smd` with its fields, 3D model, variant
  overrides and the net of each pad; nets with pad, track and via counts; per-layer track and zone counts; vias by
  size; zones with their settings; the board outline size; text and dimensions.
- Project file: every setting as a dotted path (`board.design_settings.defaults.zones.min_clearance = 0.3`); net
  classes, the sheet list and other named lists keyed by name instead of position, so adding or removing one
  shows as one line; a setting that matches KiCad 10.0.6's own default (`pro_defaults`, transcribed from the
  KiCad source - no headless KiCad here to generate a fresh project file instead) or JSON's own "nothing here"
  value (`false`, `0`, `""`, `[]`, `{}`) is folded into one summary line per top-level section instead of
  printed, so opening a project in a newer KiCad and saving it - which can add dozens of such settings - shows
  as a small diff. The table covers the zone and DRC/ERC rule-severity defaults, the ERC pin conflict matrix and
  `reuse_designators`; anything else only gets the JSON-emptiness check, which can hide a setting that is
  genuinely and meaningfully zero. `--all` always shows every line.
- Anything berc doesn't know is printed as a one-line s-expression in `# other`, so nothing is silently dropped.
  A file that isn't a KiCad s-expression comes out as it is.

`berc textconv --with-geometry FILE` adds positions (footprints rounded to 0.1 mm), wires and tracks, for when
placement is what you are reviewing. `--all` (`.kicad_pro` only) shows settings otherwise folded as looking like
KiCad's default.

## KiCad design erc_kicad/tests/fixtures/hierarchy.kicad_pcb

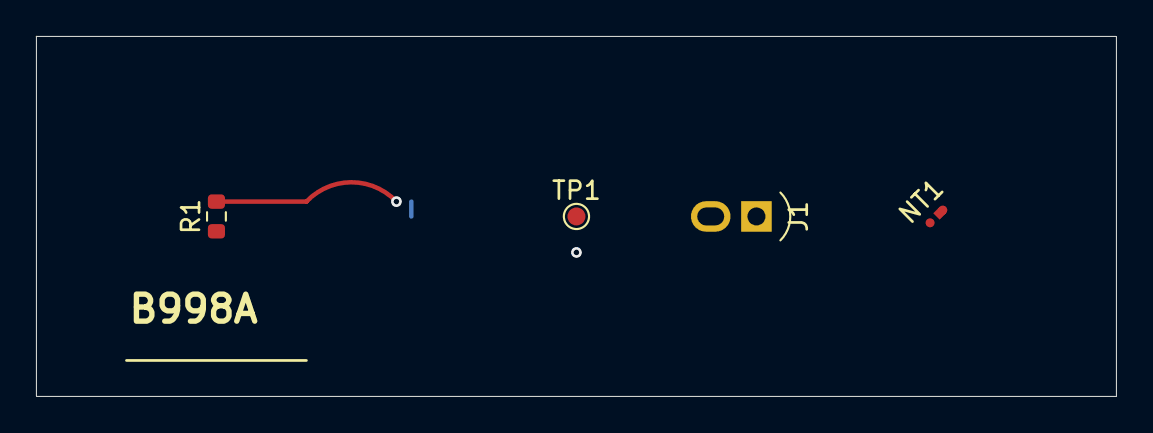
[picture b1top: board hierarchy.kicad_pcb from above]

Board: 2 copper layers, 60.0 x 20.0 mm, 5 parts (1 on the bottom side), 2 nets.

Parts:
J1: Conn_01x02; PinHeader_1x02_P2.54mm_Vertical
NT1: NetTie; NetTie-2_SMD_Pad0.5mm
R1, R5: 10k; R_0603_1608Metric
TP1: TestPoint; TestPoint_Pad_D1.0mm

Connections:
+3V3: R1.1, R5.2
GND: J1.2, NT1.1, TP1.1
